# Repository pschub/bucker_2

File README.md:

# bucker_2
2A Step-down converter demonstration

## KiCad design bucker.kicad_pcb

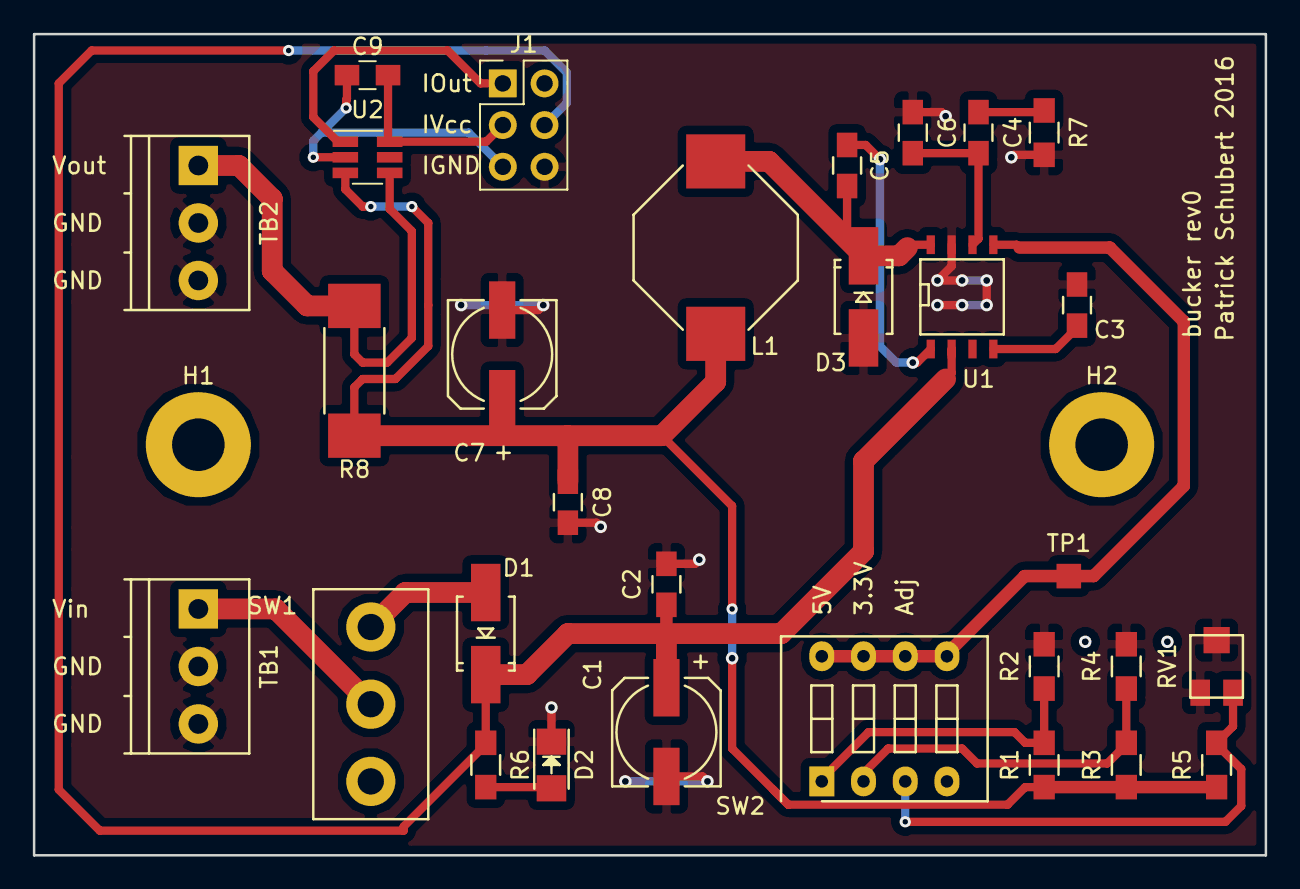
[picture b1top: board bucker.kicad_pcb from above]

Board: 2 copper layers, 75.0 x 50.0 mm, 32 parts (0 on the bottom side), 19 nets.

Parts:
C1, C7: 47uF; c_elec_6.3x4.5
C2, C8: 1uF; C_0805_HandSoldering
C3: 0.01uF; C_0805_HandSoldering
C4: 1000pF; C_0805_HandSoldering
C5, C9: 0.1uF; C_0805_HandSoldering
C6: 47pF; C_0805_HandSoldering
D1, D3: Schottky; SMA_Handsoldering
D2: RED; LED_1206
H1, H2: PLATED_HOLE; MountingHole_3.2mm_M3_Pad
J1: CONN_02X03; Pin_Header_Straight_2x03_Pitch2.54mm
L1: 22uH; SRU1038
R1, R3, R5: 10k; R_0805_HandSoldering
R2: 3.24k; R_0805_HandSoldering
R4: 1.91k; R_0805_HandSoldering
R6: 2.2k; R_0805_HandSoldering
R7: 33k; R_0805_HandSoldering
R8: 0.1; R_2512_HandSoldering
RV1: 10k; EVM-3YSX50B14
SW1: SW_SPDT; CS12ANW03
SW2: SW_DIP_x4; SW_DIP_x4_Slide
TB1, TB2: CONN_01X03; TerminalBlock_Pheonix_PT-3.5mm_3pol
TP1: TEST_1P; Measurement_Point_Square-SMD-Pad_Small
U1: TPS54231; SOIC-8-N
U2: LMP8640; SOT-23-6_Handsoldering

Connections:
/INSTR_GND: C9.1, J1.5, U2.2
/INSTR_VCC: C9.2, J1.3, U2.6
/SENSE_IN: SW2.5, SW2.6, SW2.7, SW2.8, TP1.1, U1.5
/VOUT: C7.1, C8.1, L1.2, R1.1, R3.1, R5.1, R8.2, U2.3
GND: C1.2, C2.2, C3.1, C6.1, C7.2, C8.2, D2.1, D3.2, J1.6, R2.2, R4.2, R7.2, RV1.1, RV1.2, TB1.2, TB1.3, TB2.2, TB2.3, U1.7
unnamed: C3.2, U1.4
unnamed: C4.1, R7.1
unnamed: C4.2, C6.2, U1.6
unnamed: C5.1, D3.1, L1.1, U1.8
unnamed: C5.2, U1.1
unnamed: D1.2, SW1.3
unnamed: D2.2, R6.2
unnamed: J1.1, U2.1
unnamed: R1.2, R2.1, SW2.1
unnamed: R3.2, R4.1, SW2.2
unnamed: R5.2, RV1.3, SW2.3
unnamed: R8.1, TB2.1, U2.4
unnamed: SW1.2, TB1.1
VCC: C1.1, C2.1, D1.1, J1.4, R6.1, U1.2

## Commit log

2017-02-24 Initial commit. Design 90% done.
2017-02-27 Added current sense amp and connector.
2017-02-28 Aligned mounting holes and terminal blocks.
